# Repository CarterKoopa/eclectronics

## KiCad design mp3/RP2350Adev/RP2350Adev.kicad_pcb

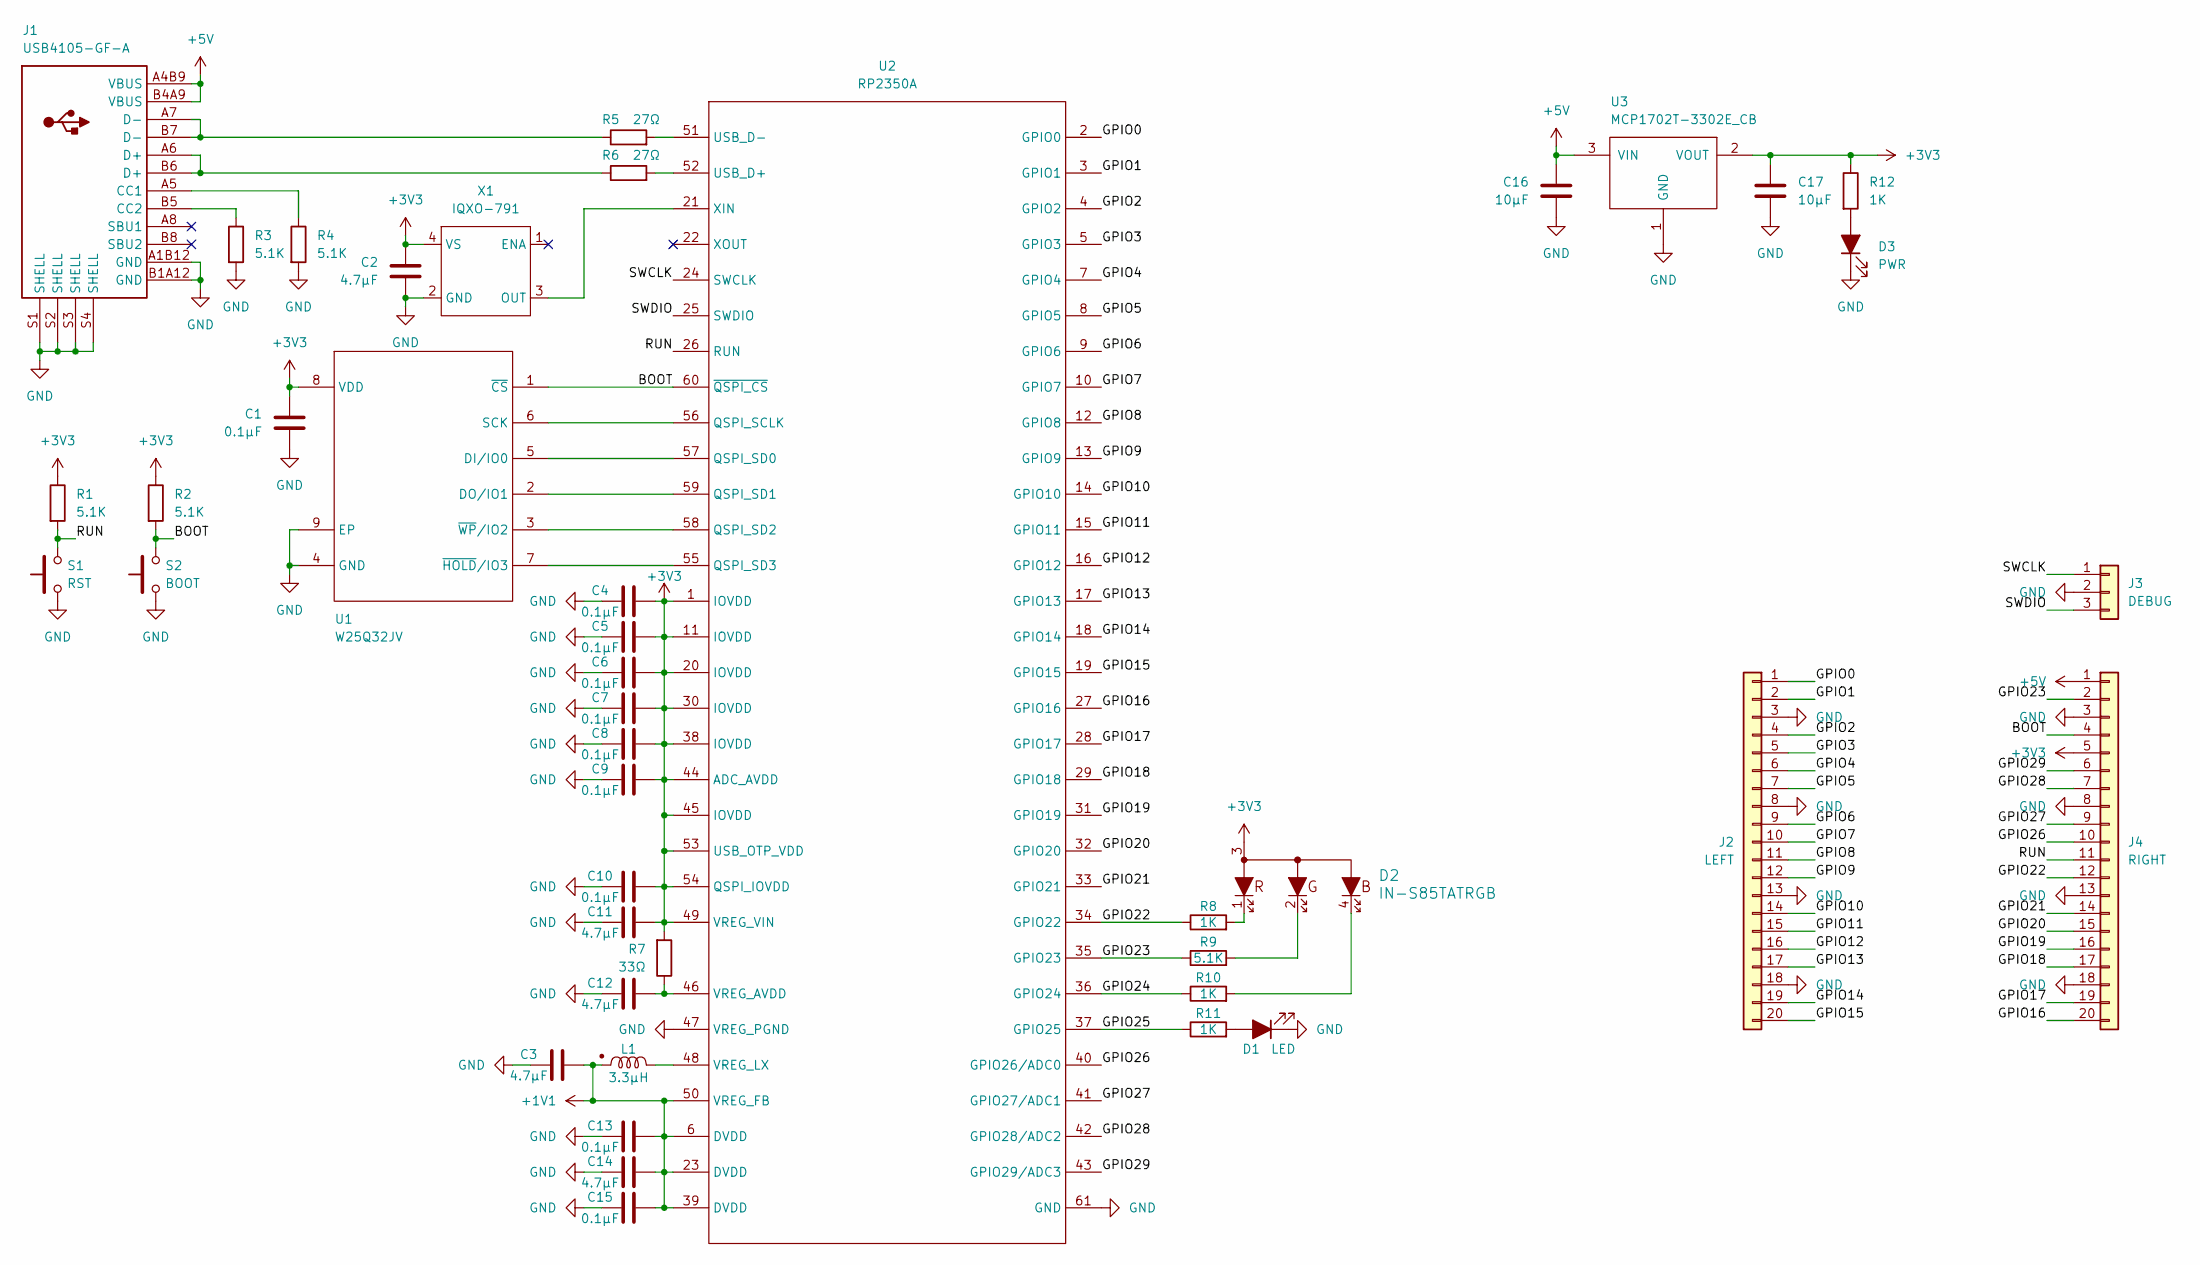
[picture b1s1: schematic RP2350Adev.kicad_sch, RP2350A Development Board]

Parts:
C1, C4, C5, C6, C7, C8, C9, C10, C13, C15: 0.1µF; C_0603_1608Metric
C2, C3, C11, C12, C14: 4.7µF; C_0603_1608Metric
C16, C17: 10µF; C_0603_1608Metric
D1: LED; LED_0805_2012Metric
D2: IN-S85TATRGB
D3: PWR; LED_0805_2012Metric
J1: USB4105-GF-A
J2: LEFT; PinHeader_1x20_P2.54mm_Vertical
J3: DEBUG; PinHeader_1x03_P2.54mm_Vertical
J4: RIGHT; PinHeader_1x20_P2.54mm_Vertical
L1: 3.3µH; AOTA-B201610S3R3-101-T
R1, R2, R3, R4, R9: 5.1K; R_0603_1608Metric
R5, R6: 27Ω; R_0603_1608Metric
R7: 33Ω; R_0603_1608Metric
R8, R10, R11, R12: 1K; R_0603_1608Metric
S1: RST; SW_SPST_B3U-1000P
S2: BOOT; SW_SPST_B3U-1000P
U1: W25Q32JV; WSON-8-1EP_6x5mm_P1.27mm_EP3.4x4.3mm
U2: RP2350A; RP2350A_QFN-60_EP_7.75x7.75_Pitch0.4mm
U3: MCP1702T-3302E_CB; SOT-23A_MC_MCH
X1: IQXO-791

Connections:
+1V1: C3.2, C13.2, C14.2, C15.2, L1.1, U2.6 (DVDD), U2.23 (DVDD), U2.39 (DVDD), U2.50 (VREG_FB)
+3V3: C1.2, C2.2, C4.2, C5.2, C6.2, C7.2, C8.2, C9.2, C10.2, C11.2, C17.1, D2.3, J4.5, R1.1, R2.1, R7.2, R12.1, U1.8 (VDD), U2.1 (IOVDD), U2.11 (IOVDD), U2.20 (IOVDD), U2.30 (IOVDD), U2.38 (IOVDD), U2.44 (ADC_AVDD), U2.45 (IOVDD), U2.49 (VREG_VIN), U2.53 (USB_OTP_VDD), U2.54 (QSPI_IOVDD), U3.2 (VOUT), X1.4 (VS)
+5V: C16.2, J1.A4B9 (VBUS), J1.B4A9 (VBUS), J4.1, U3.3 (VIN)
/BOOT: J4.4, R2.2, S2.2, U1.1 (~CS), U2.60 (~QSPI_CS)
/GPIO0: J2.1, U2.2 (GPIO0)
/GPIO1: J2.2, U2.3 (GPIO1)
/GPIO2: J2.4, U2.4 (GPIO2)
/GPIO3: J2.5, U2.5 (GPIO3)
/GPIO4: J2.6, U2.7 (GPIO4)
/GPIO5: J2.7, U2.8 (GPIO5)
/GPIO6: J2.9, U2.9 (GPIO6)
/GPIO7: J2.10, U2.10 (GPIO7)
/GPIO8: J2.11, U2.12 (GPIO8)
/GPIO9: J2.12, U2.13 (GPIO9)
/GPIO10: J2.14, U2.14 (GPIO10)
/GPIO11: J2.15, U2.15 (GPIO11)
/GPIO12: J2.16, U2.16 (GPIO12)
/GPIO13: J2.17, U2.17 (GPIO13)
/GPIO14: J2.19, U2.18 (GPIO14)
/GPIO15: J2.20, U2.19 (GPIO15)
/GPIO16: J4.20, U2.27 (GPIO16)
/GPIO17: J4.19, U2.28 (GPIO17)
/GPIO18: J4.17, U2.29 (GPIO18)
/GPIO19: J4.16, U2.31 (GPIO19)
/GPIO20: J4.15, U2.32 (GPIO20)
/GPIO21: J4.14, U2.33 (GPIO21)
/GPIO22: J4.12, R8.1, U2.34 (GPIO22)
/GPIO23: J4.2, R9.1, U2.35 (GPIO23)
/GPIO24: R10.1, U2.36 (GPIO24)
/GPIO25: R11.1, U2.37 (GPIO25)
/GPIO26: J4.10, U2.40 (GPIO26/ADC0)
/GPIO27: J4.9, U2.41 (GPIO27/ADC1)
/GPIO28: J4.7, U2.42 (GPIO28/ADC2)
/GPIO29: J4.6, U2.43 (GPIO29/ADC3)
/RUN: J4.11, R1.2, S1.2, U2.26 (RUN)
/SWCLK: J3.1, U2.24 (SWCLK); also elsewhere on the board
/SWDIO: J3.3, U2.25 (SWDIO); also elsewhere on the board
GND: C1.1, C2.1, C3.1, C4.1, C5.1, C6.1, C7.1, C8.1, C9.1, C10.1, C11.1, C12.1, C13.1, C14.1, C15.1, C16.1, C17.2, D1.1 (K), D3.1 (K), J1.A1B12 (GND), J1.B1A12 (GND), J1.S1 (SHELL), J1.S2 (SHELL), J1.S3 (SHELL), J1.S4 (SHELL), J2.3, J2.8, J2.13, J2.18, J3.2, J4.3, J4.8, J4.13, J4.18, R3.2, R4.2, S1.1, S2.1, U1.4 (GND), U1.9 (EP), U2.47 (VREG_PGND), U2.61 (GND), U3.1 (GND), X1.2 (GND); also elsewhere on the board
unnamed: D1.2 (A), R11.2
unnamed: D2.1, R8.2
unnamed: D2.2, R9.2
unnamed: D2.4, R10.2
unnamed: D3.2 (A), R12.2
unnamed: J1.A5 (CC1), R4.1
unnamed: J1.B5 (CC2), R3.1
unnamed: J1.A6 (D+), J1.B6 (D+), R6.1
unnamed: J1.A7 (D-), J1.B7 (D-), R5.1
unnamed: U1.5 (DI/IO0), U2.57 (QSPI_SD0)
unnamed: U1.2 (DO/IO1), U2.59 (QSPI_SD1)
unnamed: U1.6 (SCK), U2.56 (QSPI_SCLK)
unnamed: U1.7 (~HOLD/IO3), U2.55 (QSPI_SD3)
unnamed: U1.3 (~WP/IO2), U2.58 (QSPI_SD2)
unnamed: R6.2, U2.52 (USB_D+)
unnamed: R5.2, U2.51 (USB_D-)
unnamed: C12.2, R7.1, U2.46 (VREG_AVDD)
unnamed: L1.2, U2.48 (VREG_LX)
unnamed: U2.21 (XIN), X1.3 (OUT)

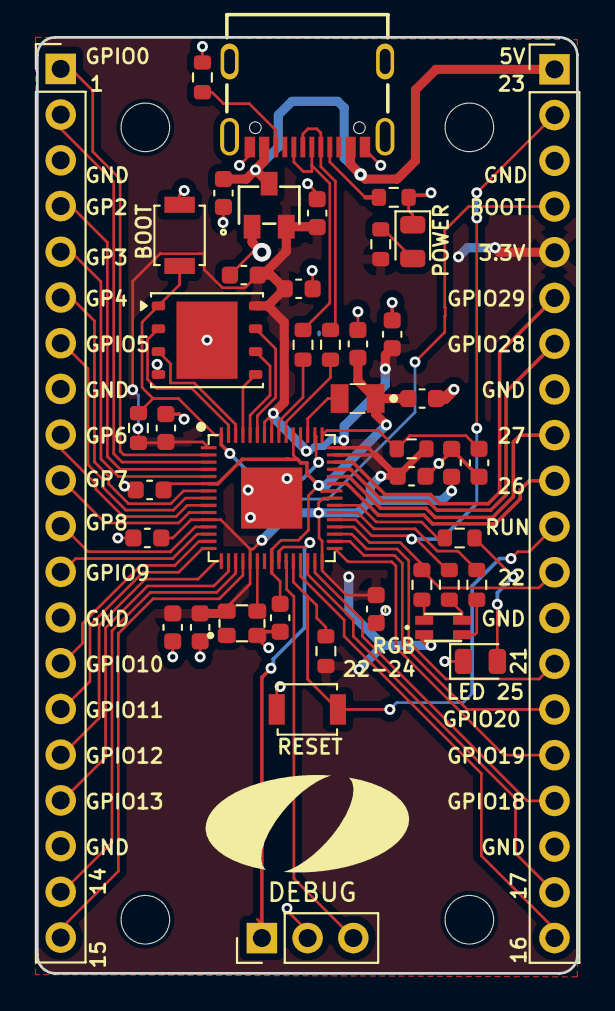
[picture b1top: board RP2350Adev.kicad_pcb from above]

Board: 2 copper layers, 30.0 x 52.0 mm, 44 parts (0 on the bottom side), 57 nets.

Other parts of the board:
DEBUG: DEBUG; PinHeader_1x03_P2.54mm_Vertical
OlinLogoLg: G***; OlinLogoLg

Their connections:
/SWCLK: DEBUG.1; also elsewhere on the board
/SWDIO: DEBUG.3; also elsewhere on the board
GND: DEBUG.2; also elsewhere on the board

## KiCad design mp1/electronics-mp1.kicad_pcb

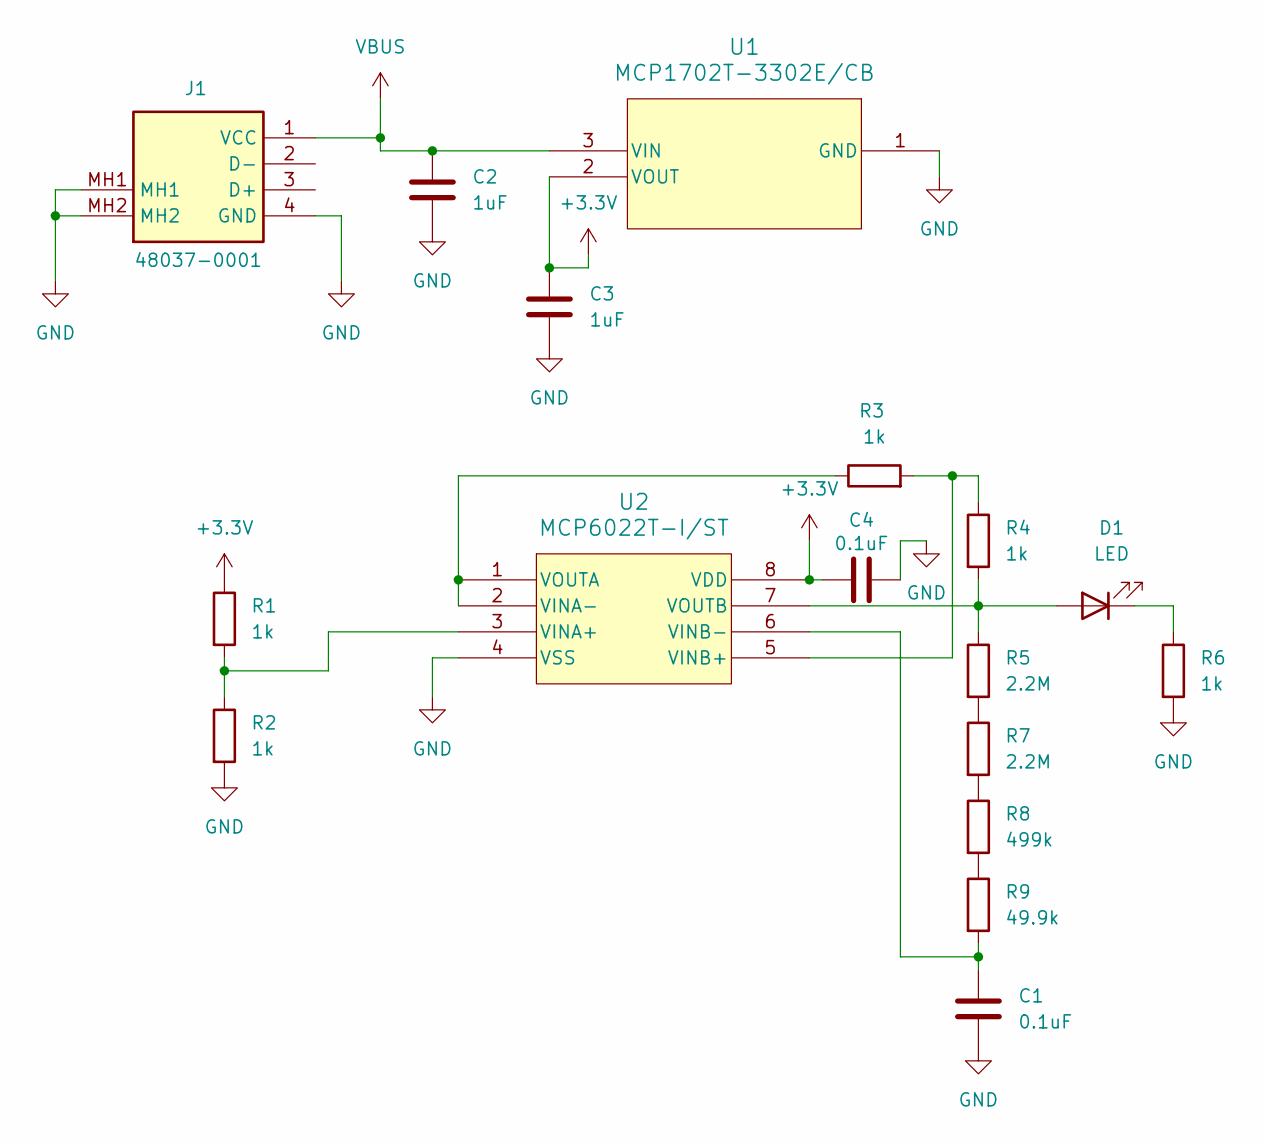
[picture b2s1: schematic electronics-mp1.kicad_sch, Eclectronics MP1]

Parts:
C1, C4: 0.1uF; C_0603_1608Metric; MPN CC0603JRX7R9BB104; DigikeyPN 311-1779-1-ND
C2, C3: 1uF; C_0603_1608Metric; MPN C0603C105K3RACTU; DigikeyPN 399-7376-1-ND
D1: LED; LED_0805_2012Metric; MPN LTST-C171KRKT; DigikeyPN 160-1427-1-ND
J1: 48037-0001; 480370001; MPN 48037-0001; DigikeyPN WM17117-ND
R1, R2, R3, R4, R6: 1k; R_0603_1608Metric; MPN RC0603FR-071KL; DigikeyPN 311-1.00KHRCT-ND
R5, R7: 2.2M; R_0603_1608Metric; MPN RC0603FR-072ML; DigikeyPN 311-2.00MHRCT-ND
R8: 499k; R_0603_1608Metric; MPN RC0603FR-07499KL; DigikeyPN 311-499KHRCT-ND
R9: 49.9k; R_0603_1608Metric; MPN RC0603FR-0749K9L; DigikeyPN 311-49.9KHRCT-ND
U1: MCP1702T-3302E/CB; SOT-23A_MC_MCH; MPN MCP1702T-3302E/CB; DigikeyPN MCP1702T-3302E/CBCT-ND
U2: MCP6022T-I/ST; TSSOP8_MC_MCH; MPN MCP6022T-I/ST; DigikeyPN MCP6022T-I/STCT-ND

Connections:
+3.3V: C3.1, C4.1, R1.1, U1.2 (VOUT), U2.8 (VDD)
GND: C1.2, C2.2, C3.2, C4.2, J1.4 (GND), J1.MH1, J1.MH2, R2.2, R6.2, U1.1 (GND), U2.4 (VSS)
unnamed: D1.2 (A), R4.2, R5.1, U2.7 (VOUTB)
unnamed: D1.1 (K), R6.1
unnamed: R5.2, R7.1
unnamed: R7.2, R8.1
unnamed: R8.2, R9.1
unnamed: R1.2, R2.1, U2.3 (VINA+)
unnamed: R3.1, U2.1 (VOUTA), U2.2 (VINA-)
unnamed: R3.2, R4.1, U2.5 (VINB+)
unnamed: C1.1, R9.2, U2.6 (VINB-)
VBUS: C2.1, J1.1 (VCC), U1.3 (VIN)

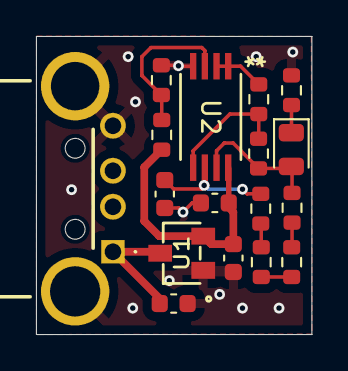
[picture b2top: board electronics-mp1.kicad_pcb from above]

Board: 2 copper layers, 15.3 x 16.6 mm, 17 parts (0 on the bottom side), 12 nets.

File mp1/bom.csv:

Reference,Qty,Value,Description,MPN,DigikeyPN
D1,1,LED,Light emitting diode,LTST-C171KRKT,160-1427-1-ND
"R1,R2,R3,R4,R6",5,1k,Resistor,RC0603FR-071KL,311-1.00KHRCT-ND
"R5,R7",2,2.2M,Resistor,RC0603FR-072ML,311-2.00MHRCT-ND
R9,1,49.9k,Resistor,RC0603FR-0749K9L,311-49.9KHRCT-ND
R8,1,499k,Resistor,RC0603FR-07499KL,311-499KHRCT-ND
"C1,C4",2,0.1uF,Unpolarized capacitor,CC0603JRX7R9BB104,311-1779-1-ND
"C2,C3",2,1uF,Unpolarized capacitor,C0603C105K3RACTU,399-7376-1-ND
U2,1,MCP6022T-I/ST,Dual Rail-to-Rail Opamp,MCP6022T-I/ST,MCP6022T-I/STCT-ND
U1,1,MCP1702T-3302E/CB,3.3V Linear Regulator,MCP1702T-3302E/CB,MCP1702T-3302E/CBCT-ND
J1,1,48037-0001,"USB Type A Plug Through Hole Right Angle Molex Male 1 Port Right Angle Through Hole Type A USB Connector, 150 V ac, 1.5A 48037",48037-0001,WM17117-ND

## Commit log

2026-02-10 Add MP1 initial commit
2026-02-10 Add non-standard symbols and foorptins
2026-02-10 Update report with KiCAD symbol notes
2026-02-10 Add BOM
2026-02-10 Add LTspice data output
2026-02-10 Add LTspice simulation
2026-02-10 Add PDF outputs
2026-03-02 Initial commit MP3
2026-03-05 Update silkscreen thickness/width for DRC
2026-03-05 Update silkscreen overlap
2026-03-05 Update minimum via size to 24 mils
2026-03-05 Update missed undersized vias to 24 mils
2026-03-05 Update ground pad vias to 24 mils
2026-03-05 Remove redundant traces
2026-03-05 Update power trace widths to ~20 mils
2026-03-05 Fix new trace width DRC errors
2026-03-05 Update board sizing to be 50x32mm
2026-03-05 Add mounting holes
2026-03-05 Update mounting holes for DRC
2026-03-05 Nudge bottom layer traces
2026-03-08 Remove Custom Rules from PCBWay
2026-03-09 Relocate flash and buck components
